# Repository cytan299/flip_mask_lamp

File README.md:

# Remote controlled flip Bahtinov mask and lamp

by C.Y. Tan 2017

I made a flip mask and lamp for my FSQ106 so that when they are
mounted on the telescope, they will balance each other out when mounted on
the opposite side of the telescope.

## Design

The flip mask and lamp are designed as a master and slave pair. I have
chosen the flip mask controller to be the master and the flip lamp
controller to be the slave.

The mechanical design of the flip mask and lamp are mirror images of
each other. The principal parts used in the design are as follows:

* A servo controller made by Pololu called the [Maestro](https://www.pololu.com/product/1350).
* A servo that rotates greater than 270
degrees: the [Feetech FR5311M](http://www.feetechrc.com/product/continuous-rotation-servo/two-working-mode-digital-programmable-metal-gears-servo-fr5311m/).
* A [sprocket and chain system](https://www.servocity.com/0-1227-pitch-nylon-servo-sprockets) for connecting the servo to the mask and lamp.
* Interlock switches to indicate where the mask or lamp is
  * A mechanical lever switch
  * A Hall switch
* A lamp made from an
[electroluminescent panel with dimmer and power inverter](https://knema.com/collections/electroluminescent-el-panels/products/electroluminescent-panel-split-electrode-type-blue-green-or-white-includes-power-supply-and-dimming-inverter).
* Filter sheets have been added so that the RGB components of the EL panel have nearly
  the same intensities.

## Movie

A movie of how the flip mask and lamp in action can be found on [youtube](https://youtu.be/KrSrh4rIldk).

## Support

This is unsupported hardware. Build at your own peril! :)

You can submit questions or bug reports using the
[issues](https://github.com/cytan299/flip_mask_lamp/issues) tab on
the right and then click on **NEW**.

Have fun!

## Directory structure

* **howto** Assembly instructions for the flip mask and lamp.
* **ponoko** The files that are used for laser cutting the acrylic parts of
the design. These files can be sent directly to
[Ponoko](http://www.ponoko.com) for laser cutting.
* **bom** Bill of materials for 1 pair of flip mask and lamp.
* **eagle** Eagle schematic and board files.
* **python** Source code for the python control program.
* **pics** Photographs used in the README's and Wiki.

## Other information

More information can be found in he *README.md* files in each
directory and the [wiki](https://github.com/cytan299/flip_mask_lamp/wiki/Flip-Mask-and-Lamp) of this project on github.

## Copyright
All the software, documentation, and hardware that I have written is
copyright 2017 C.Y. Tan.

All software is released under GPLv3

All documentation is released under Creative Commons
Attribution-ShareAlike 3.0 Unported License or GNU Free
Documentation License, Version 1.3

All hardware is released under CERN Hardware Open License v1.2

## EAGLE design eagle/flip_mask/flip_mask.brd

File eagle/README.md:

# Eagle files

These are the eagle files that can be sent to pc board manufacturers to
be made. There is a free version of [eagle](http://cadsoftusa.com)
that can be downloaded to view the designs.

## Directories

* **flip_mask** The flip mask control unit. This unit 
  * controls the Bahtinov mask
  * is the master that controls the flip lamp unit that is the slave unit
  * contains the USB interface
  * has the [Maestro](https://www.pololu.com/product/1350) servo controller
* **flip_lamp** The flip lamp control unit. This unit
  * controls the lamp

## Copyright

The schematic and board designs are copyright 2017 C.Y. Tan and
released under the CERN Open Hardware License v1.2

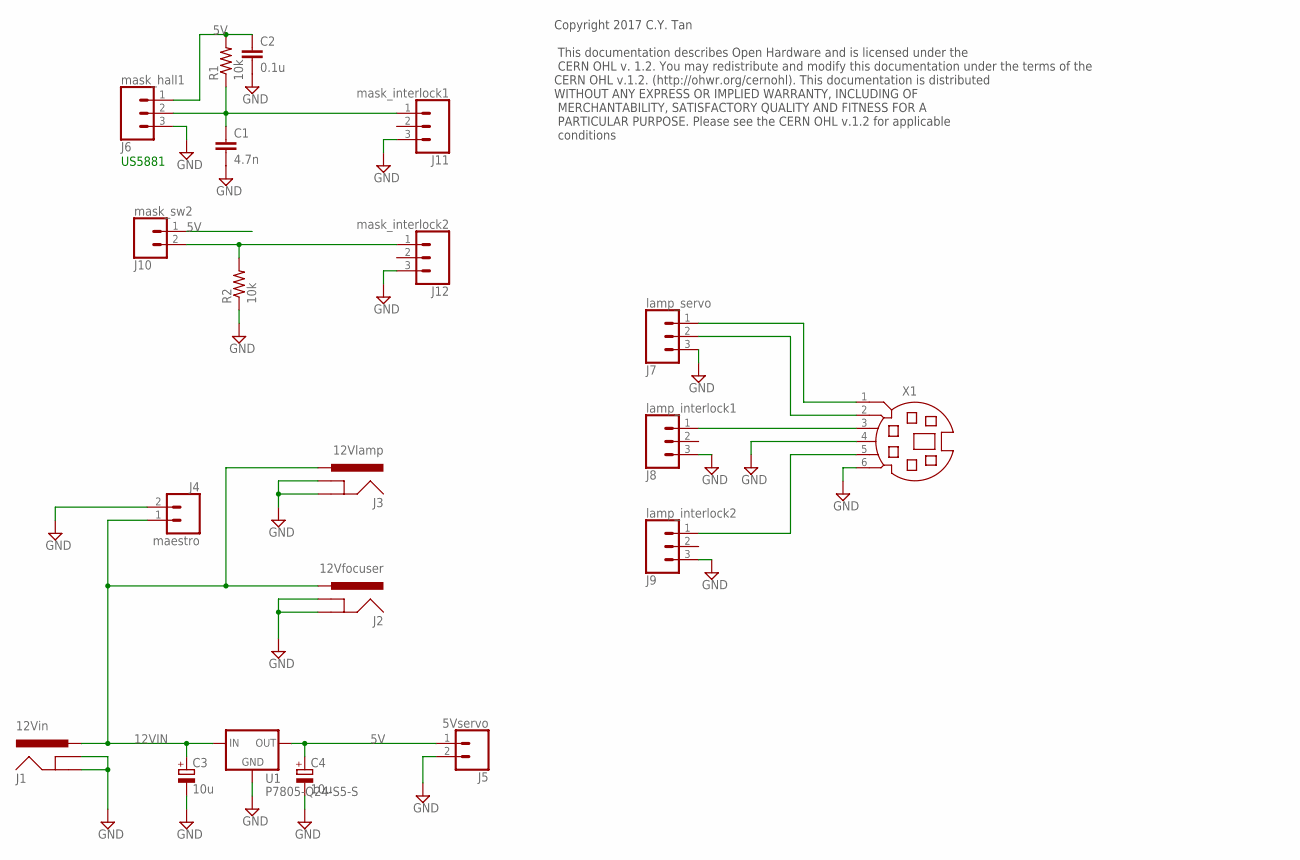
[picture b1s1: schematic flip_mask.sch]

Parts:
C1: 4.7n; CAP-PTH-5MM
C2: 0.1u; CAP-PTH-5MM
C3, C4: 10u; E2,5-6
J1: 12Vin; POWER_JACK_PTH
J2: 12Vfocuser; POWER_JACK_PTH
J3: 12Vlamp; POWER_JACK_PTH
J4: maestro; 1X02
J5: 5Vservo; 1X02
J6: mask_hall1; 1X03
J7: lamp_servo; 1X03
J8: lamp_interlock1; 1X03
J9: lamp_interlock2; 1X03
J10: mask_sw2; 1X02
J11: mask_interlock1; 1X03
J12: mask_interlock2; 1X03
R1, R2: 10k; 0207/10
U1: P7805-Q24-S5-S; DC-DC_CONVERTER_78XX
X1: MD06SS; MDIN06SS

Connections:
5V: C2.1, C4.+, J5.1, J6.1, J10.1, R1.2, U1.VOUT (OUT)
12VIN: C3.+, J1.PWR, J2.PWR, J3.PWR, J4.1, U1.VIN (IN)
GND: C1.2, C2.2, C3.-, C4.-, J1.GND, J1.GNDBREAK, J2.GND, J2.GNDBREAK, J3.GND, J3.GNDBREAK, J4.2, J5.2, J6.3, J7.3, J8.3, J9.3, J11.3, J12.3, R2.1, U1.GND, X1.4, X1.6
unnamed: C1.1, J6.2, J11.1, R1.1
unnamed: J7.2, X1.2
unnamed: J8.1, X1.3
unnamed: J10.2, J12.1, R2.2
unnamed: J7.1, X1.1
unnamed: J9.1, X1.5

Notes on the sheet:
US5881
Copyright 2017 C.Y. Tan This documentation describes Open Hardware and is licensed under the CERN OHL v. 1.2. You may redistribute and modify this documentation under the terms of the CERN OHL v.1.2. (http://ohwr.org/cernohl). This documentation is distributed WITHOUT ANY EXPRESS OR IMPLIED WARRANT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

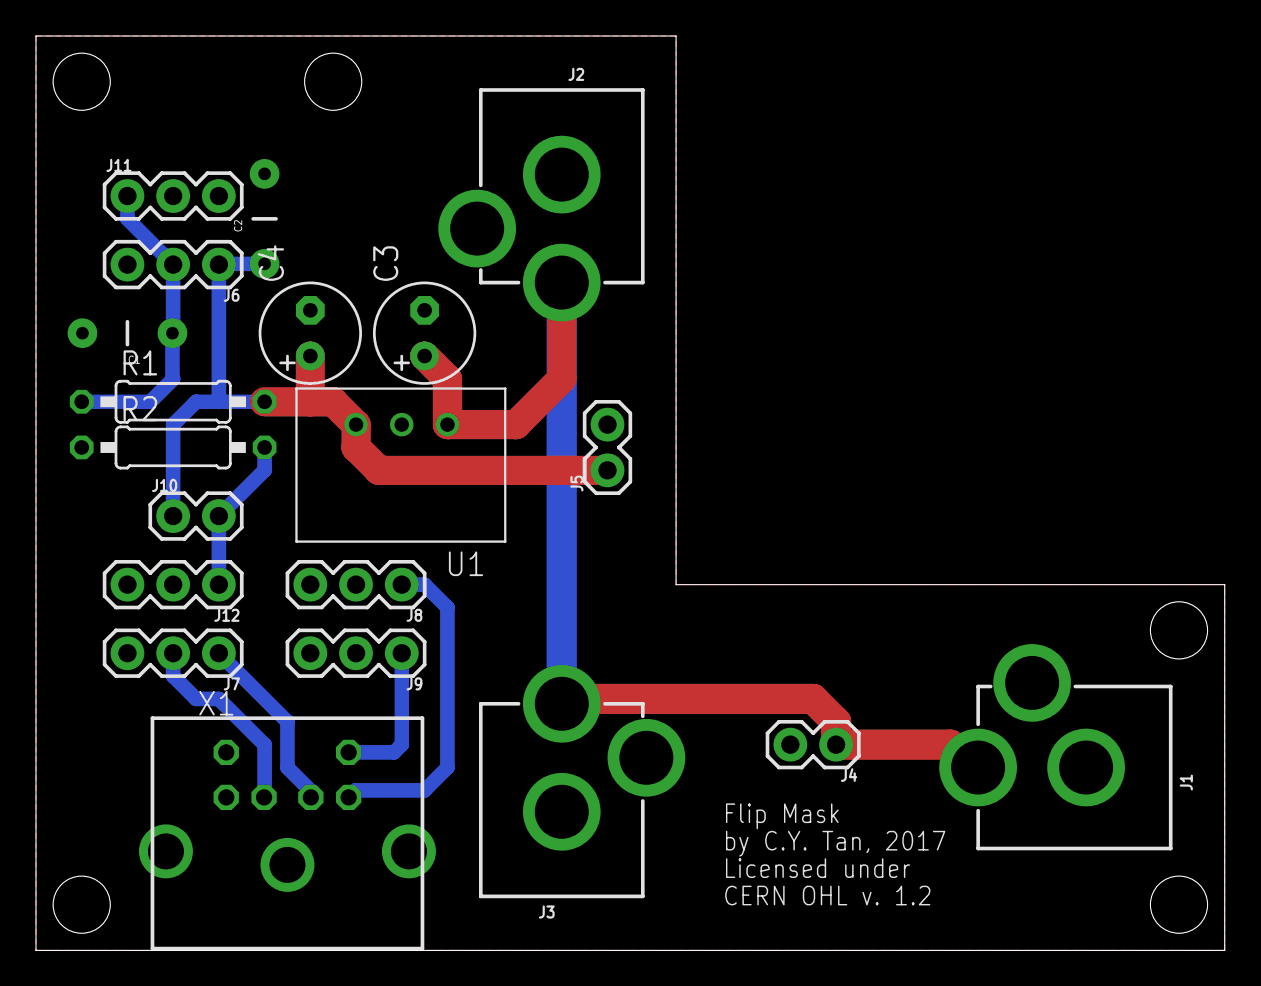
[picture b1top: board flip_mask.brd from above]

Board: 2 copper layers, 66.0 x 50.8 mm, 20 parts (0 on the bottom side), 9 nets.

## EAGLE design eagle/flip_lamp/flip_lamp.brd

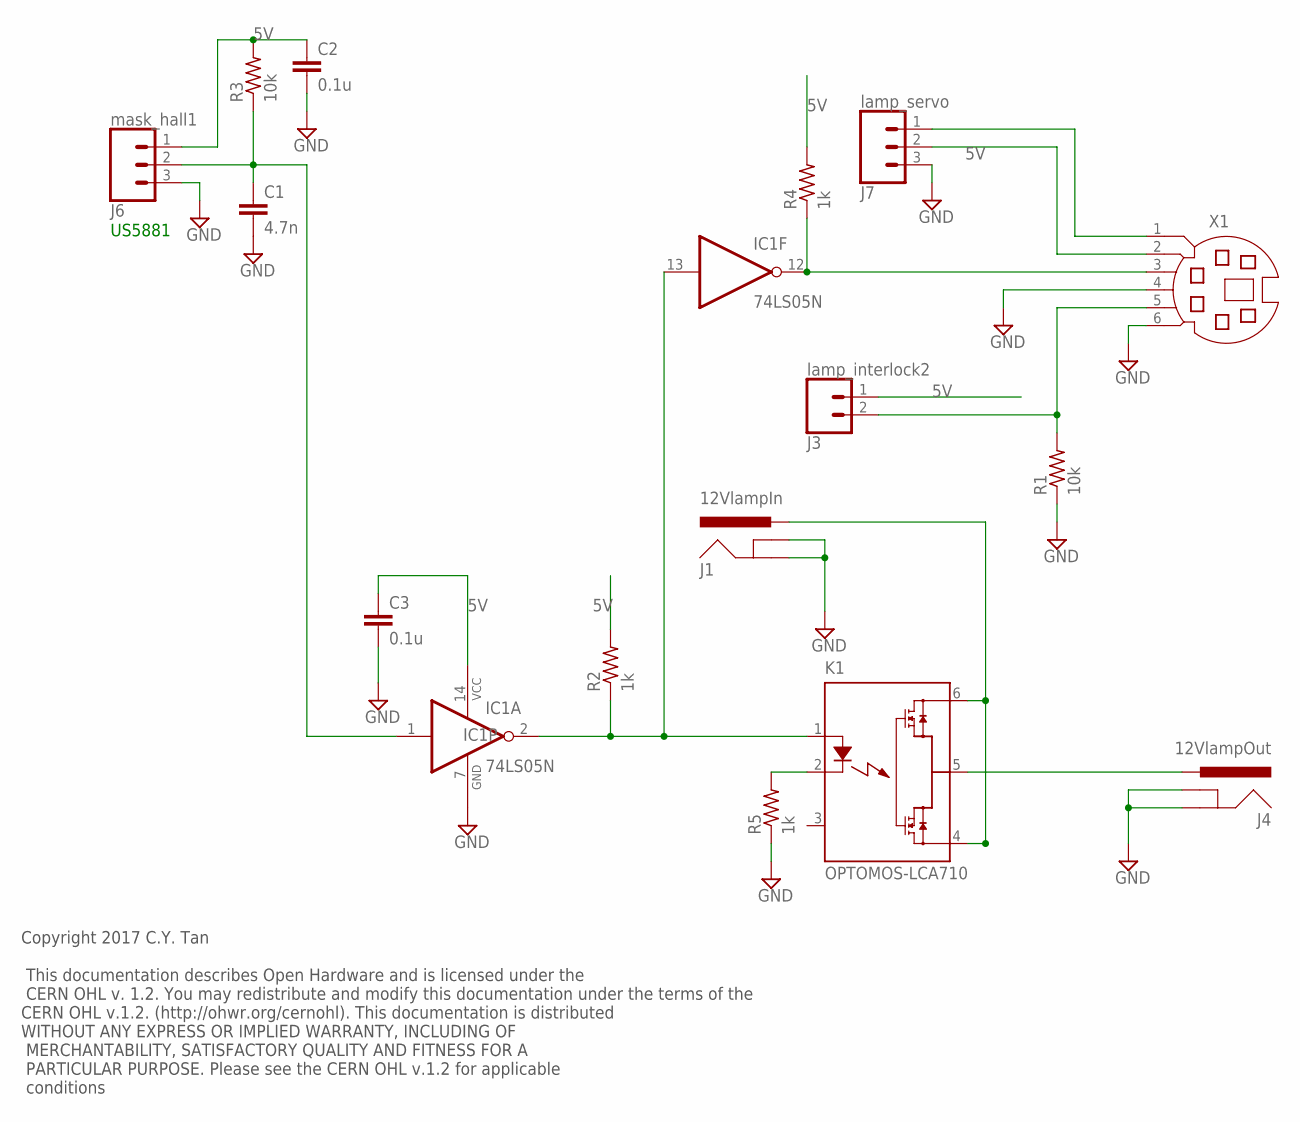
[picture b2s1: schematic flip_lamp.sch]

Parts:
C1: 4.7n; CAP-PTH-5MM
C2, C3: 0.1u; CAP-PTH-5MM
IC1: 74LS05N; DIL14
J1: 12VlampIn; POWER_JACK_PTH
J3: lamp_interlock2; 1X02
J4: 12VlampOut; POWER_JACK_PTH
J6: mask_hall1; 1X03
J7: lamp_servo; 1X03
K1: OPTOMOS-LCA710; DIL6
R1, R3: 10k; 0207/10
R2, R4, R5: 1k; 0207/10
X1: MD06SS; MDIN06SS

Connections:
5V: C2.1, C3.1, IC1.14 (VCC), J3.1, J6.1, J7.2, R2.2, R3.2, R4.2, X1.2
GND: C1.2, C2.2, C3.2, IC1.7 (GND), J1.GND, J1.GNDBREAK, J4.GND, J4.GNDBREAK, J6.3, J7.3, R1.1, R5.1, X1.4, X1.6
unnamed: IC1.12 (O), R4.1, X1.3
unnamed: J1.PWR, K1.4 (DS3), K1.6 (DS1)
unnamed: J4.PWR, K1.5 (DS2)
unnamed: IC1.2 (O), IC1.13 (I), K1.1 (A), R2.1
unnamed: J7.1, X1.1
unnamed: J3.2, R1.2, X1.5
unnamed: K1.2 (K), R5.2
unnamed: C1.1, IC1.1 (I), J6.2, R3.1

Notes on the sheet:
US5881
Copyright 2017 C.Y. Tan This documentation describes Open Hardware and is licensed under the CERN OHL v. 1.2. You may redistribute and modify this documentation under the terms of the CERN OHL v.1.2. (http://ohwr.org/cernohl). This documentation is distributed WITHOUT ANY EXPRESS OR IMPLIED WARRANT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

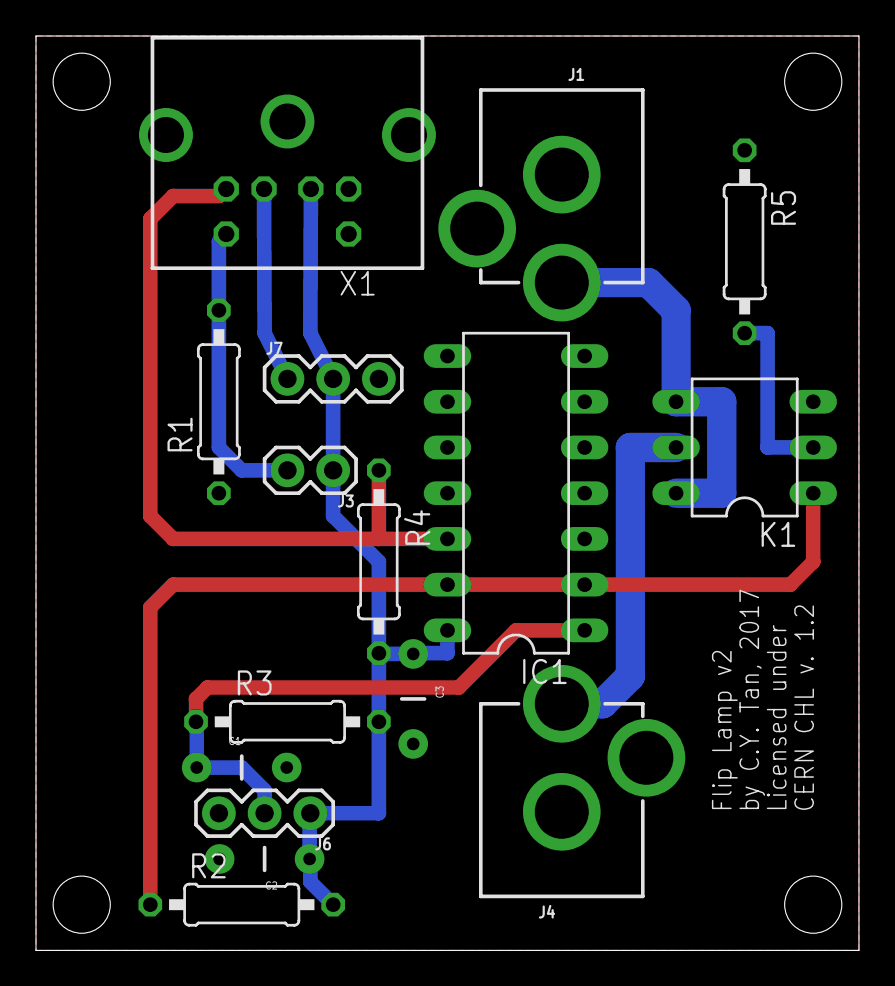
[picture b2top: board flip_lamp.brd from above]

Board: 2 copper layers, 45.7 x 50.8 mm, 16 parts (0 on the bottom side), 10 nets.

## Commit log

2017-09-04 First commit of flip mask and lamp
2017-09-04 More updates to README.md
2017-09-04 Added eagle/README.md
2017-09-04 Updated eagle/README.md
2017-11-19 Added instructions in assembly.pdf and updated the bill of materials bom.ods for filter sheets.
2019-10-04 removed and re-added python/flipit subdirectory so that python files are in repo

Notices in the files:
parts and their libraries:
SparkFun-Connectors: Licensing: Creative Commons ShareAlike 4.0 International - https://creativecommons.org/licenses/by-sa/4.0
